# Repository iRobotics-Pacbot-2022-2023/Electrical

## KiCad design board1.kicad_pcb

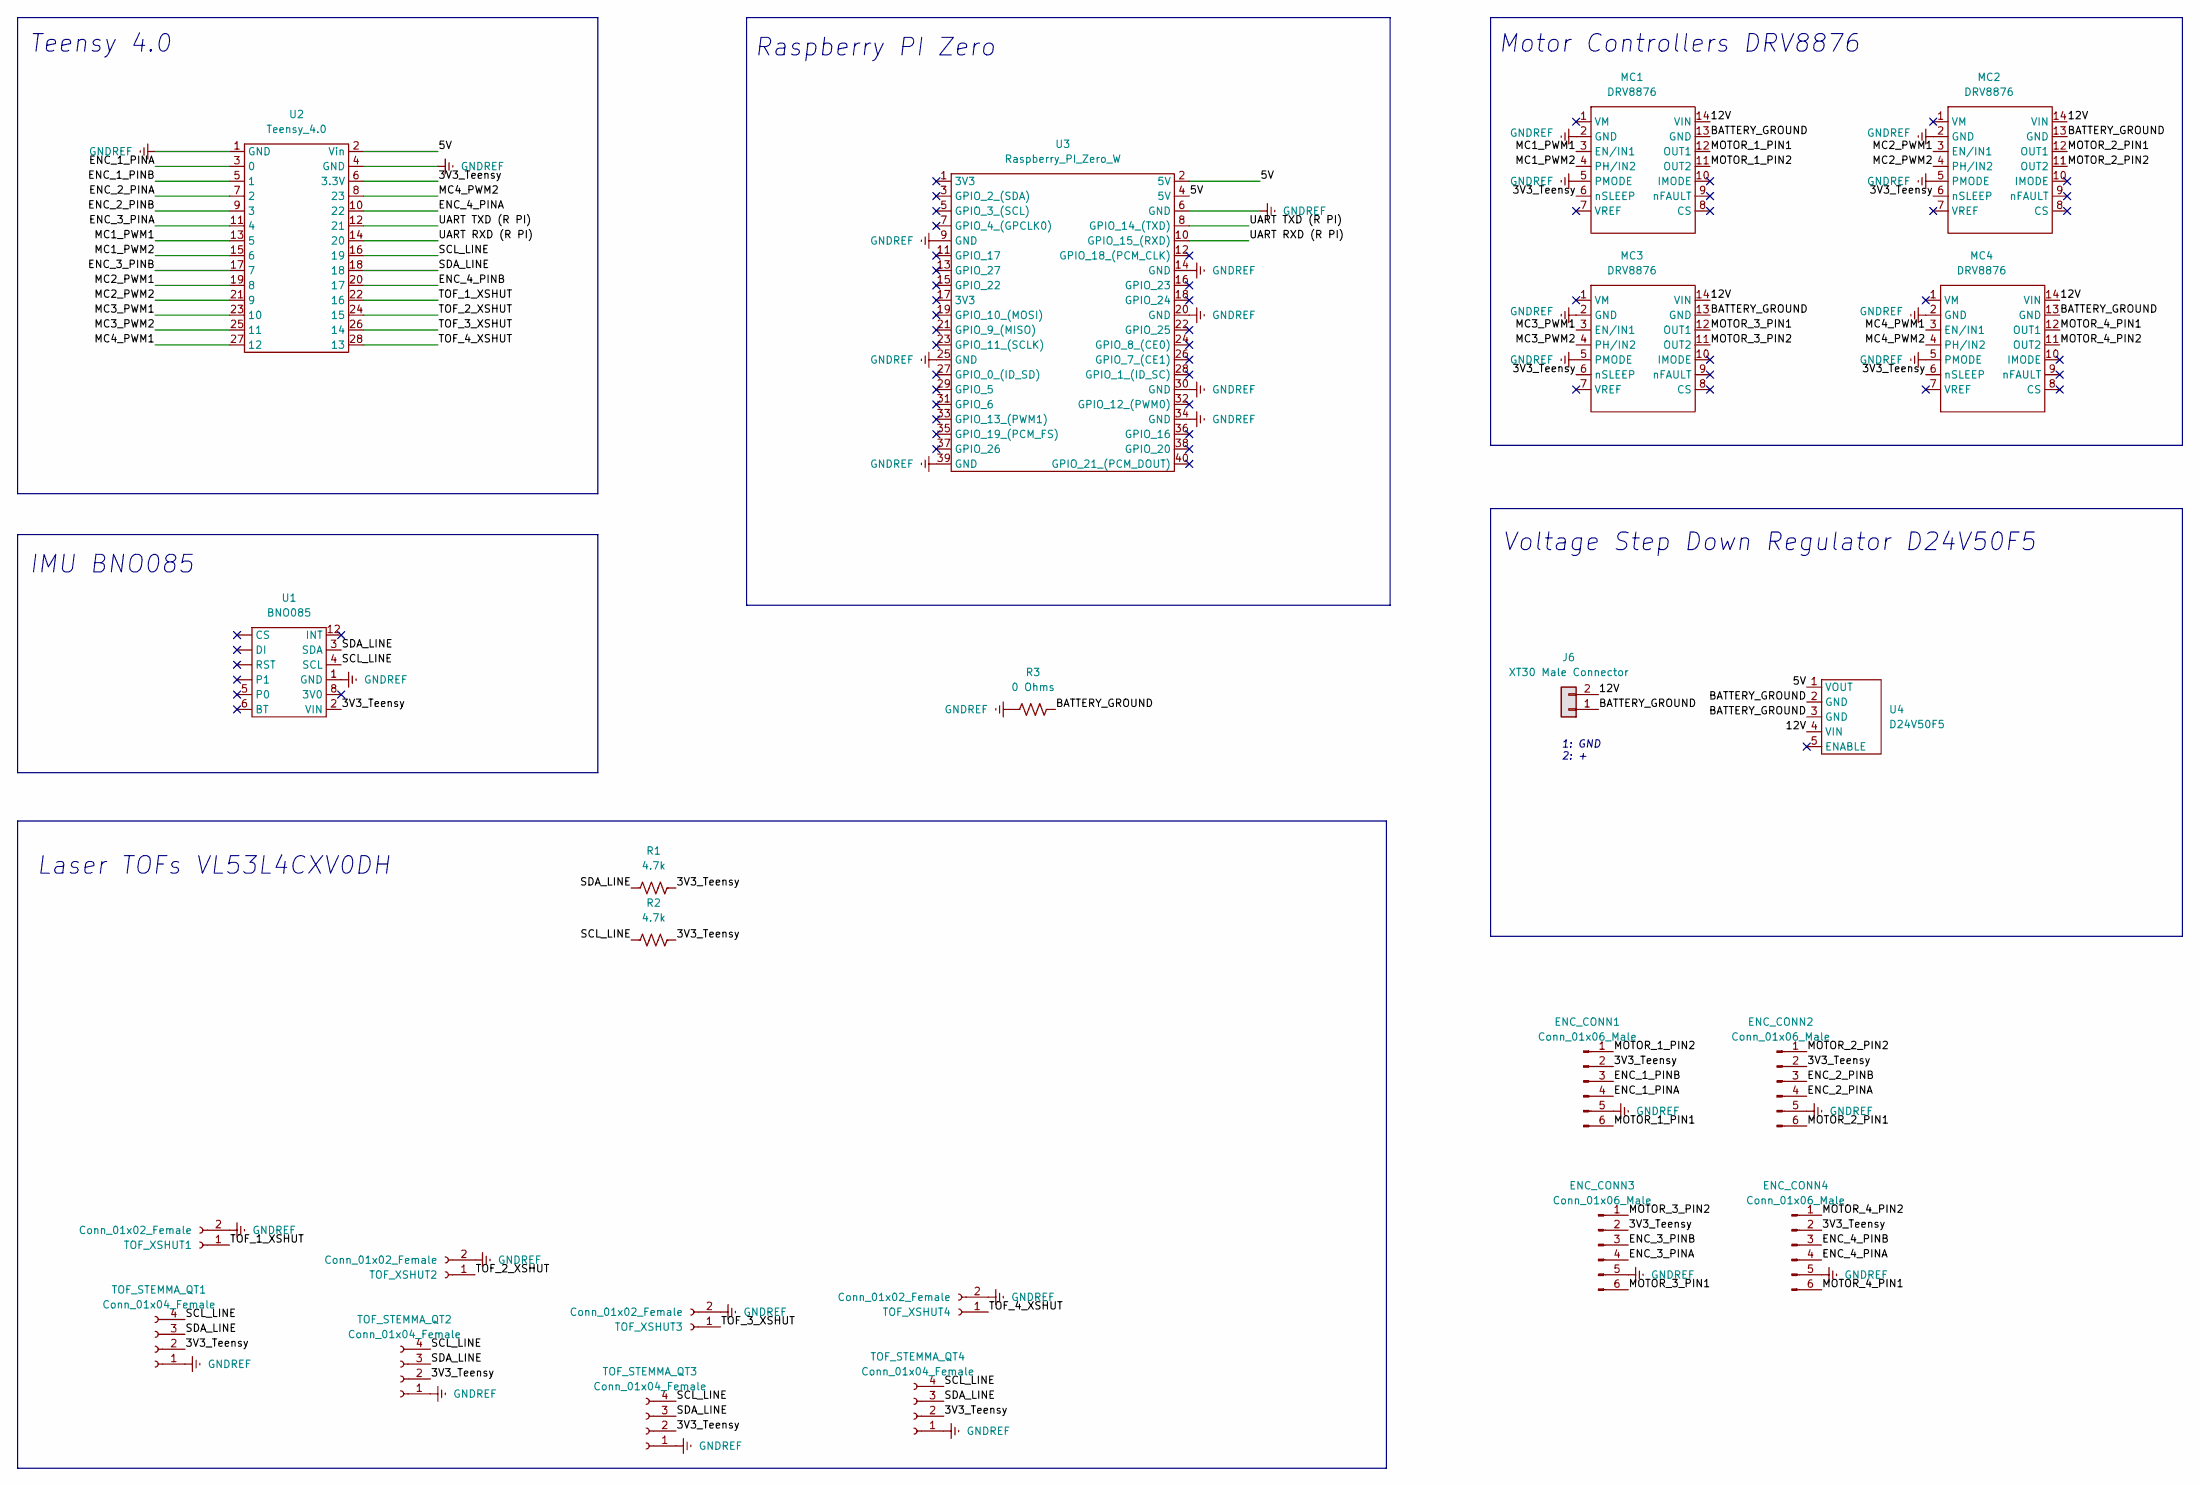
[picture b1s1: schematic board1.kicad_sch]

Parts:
ENC_CONN1: Conn_01x06_Male; PinHeader_1x06_P2.54mm_Vertical
ENC_CONN2, ENC_CONN3, ENC_CONN4: Conn_01x06_Male; PinSocket_1x06_P2.54mm_Vertical
J6: XT30 Male Connector; AMASS_XT30U-M_1x02_P5.0mm_Vertical
MC1, MC2, MC3, MC4: DRV8876
R1, R2: 4.7k; R_0805_2012Metric
R3: 0 Ohms; R_0805_2012Metric
TOF_STEMMA_QT1, TOF_STEMMA_QT2, TOF_STEMMA_QT3, TOF_STEMMA_QT4: Conn_01x04_Female; JST_SH_BM04B-SRSS-TB_1x04-1MP_P1.00mm_Vertical
TOF_XSHUT1, TOF_XSHUT2, TOF_XSHUT3, TOF_XSHUT4: Conn_01x02_Female; PinSocket_1x02_P2.54mm_Vertical
U1: BNO085; JST_SH_BM04B-SRSS-TB_1x04-1MP_P1.00mm_Vertical
U2: Teensy_4.0; Teensy 4.0
U3: Raspberry_PI_Zero_W; Raspberry Pi Zero W
U4: D24V50F5; Voltage Regulator D24V50F5

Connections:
/3V3_Teensy: ENC_CONN1.2, ENC_CONN2.2, ENC_CONN3.2, ENC_CONN4.2, MC1.6 (nSLEEP), MC2.6 (nSLEEP), MC3.6 (nSLEEP), MC4.6 (nSLEEP), R1.2, R2.2, TOF_STEMMA_QT1.2, TOF_STEMMA_QT2.2, TOF_STEMMA_QT3.2, TOF_STEMMA_QT4.2, U1.2 (VIN), U2.6 (3.3V)
/5V: U2.2 (Vin), U3.2 (5V), U3.4 (5V), U4.1 (VOUT)
/12V: J6.2, MC1.14 (VIN), MC2.14 (VIN), MC3.14 (VIN), MC4.14 (VIN), U4.4 (VIN)
/BATTERY_GROUND: J6.1, MC1.13 (GND), MC2.13 (GND), MC3.13 (GND), MC4.13 (GND), R3.2, U4.2 (GND), U4.3 (GND)
/ENC_1_PINA: ENC_CONN1.4, U2.3 (0)
/ENC_1_PINB: ENC_CONN1.3, U2.5 (1)
/ENC_2_PINA: ENC_CONN2.4, U2.7 (2)
/ENC_2_PINB: ENC_CONN2.3, U2.9 (3)
/ENC_3_PINA: ENC_CONN3.4, U2.11 (4)
/ENC_3_PINB: ENC_CONN3.3, U2.17 (7)
/ENC_4_PINA: ENC_CONN4.4, U2.10 (22)
/ENC_4_PINB: ENC_CONN4.3, U2.20 (17)
/MC1_PWM1: MC1.3 (EN/IN1), U2.13 (5)
/MC1_PWM2: MC1.4 (PH/IN2), U2.15 (6)
/MC2_PWM1: MC2.3 (EN/IN1), U2.19 (8)
/MC2_PWM2: MC2.4 (PH/IN2), U2.21 (9)
/MC3_PWM1: MC3.3 (EN/IN1), U2.23 (10)
/MC3_PWM2: MC3.4 (PH/IN2), U2.25 (11)
/MC4_PWM1: MC4.3 (EN/IN1), U2.27 (12)
/MC4_PWM2: MC4.4 (PH/IN2), U2.8 (23)
/MOTOR_1_PIN1: ENC_CONN1.6, MC1.12 (OUT1)
/MOTOR_1_PIN2: ENC_CONN1.1, MC1.11 (OUT2)
/MOTOR_2_PIN1: ENC_CONN2.6, MC2.12 (OUT1)
/MOTOR_2_PIN2: ENC_CONN2.1, MC2.11 (OUT2)
/MOTOR_3_PIN1: ENC_CONN3.6, MC3.12 (OUT1)
/MOTOR_3_PIN2: ENC_CONN3.1, MC3.11 (OUT2)
/MOTOR_4_PIN1: ENC_CONN4.6, MC4.12 (OUT1)
/MOTOR_4_PIN2: ENC_CONN4.1, MC4.11 (OUT2)
/SCL_LINE: R2.1, TOF_STEMMA_QT1.4, TOF_STEMMA_QT2.4, TOF_STEMMA_QT3.4, TOF_STEMMA_QT4.4, U1.4 (SCL), U2.16 (19)
/SDA_LINE: R1.1, TOF_STEMMA_QT1.3, TOF_STEMMA_QT2.3, TOF_STEMMA_QT3.3, TOF_STEMMA_QT4.3, U1.3 (SDA), U2.18
/TOF_1_XSHUT: TOF_XSHUT1.1, U2.22 (16)
/TOF_2_XSHUT: TOF_XSHUT2.1, U2.24 (15)
/TOF_3_XSHUT: TOF_XSHUT3.1, U2.26 (14)
/TOF_4_XSHUT: TOF_XSHUT4.1, U2.28 (13)
/UART RXD (R PI): U2.14 (20), U3.10 (GPIO_15_(RXD))
/UART TXD (R PI): U2.12 (21), U3.8 (GPIO_14_(TXD))
GNDREF: ENC_CONN1.5, ENC_CONN2.5, ENC_CONN3.5, ENC_CONN4.5, MC1.2 (GND), MC1.5 (PMODE), MC2.2 (GND), MC2.5 (PMODE), MC3.2 (GND), MC3.5 (PMODE), MC4.2 (GND), MC4.5 (PMODE), R3.1, TOF_STEMMA_QT1.1, TOF_STEMMA_QT2.1, TOF_STEMMA_QT3.1, TOF_STEMMA_QT4.1, TOF_XSHUT1.2, TOF_XSHUT2.2, TOF_XSHUT3.2, TOF_XSHUT4.2, U1.1 (GND), U2.1 (GND), U2.4 (GND), U3.6 (GND), U3.9 (GND), U3.14 (GND), U3.20 (GND), U3.25 (GND), U3.30 (GND), U3.34 (GND), U3.39 (GND)

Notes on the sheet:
Laser TOFs VL53L4CXV0DH
Teensy 4.0
1: GND 2: +
Motor Controllers DRV8876
Raspberry PI Zero
IMU BNO085
Voltage Step Down Regulator D24V50F5

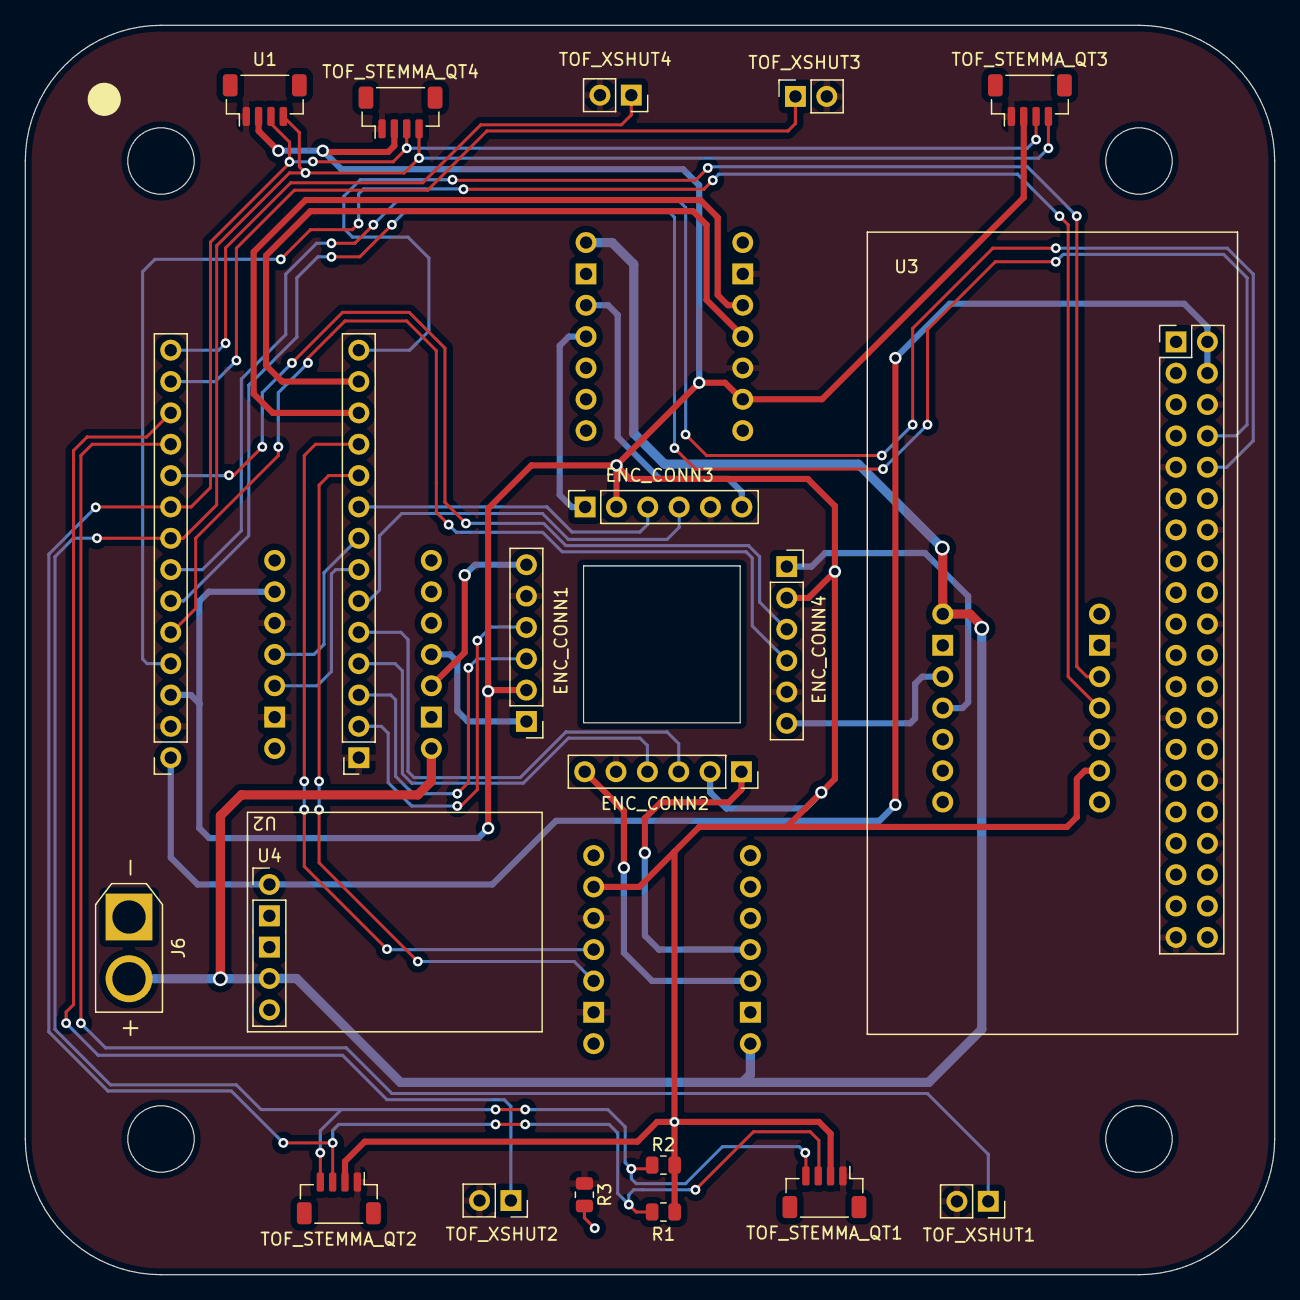
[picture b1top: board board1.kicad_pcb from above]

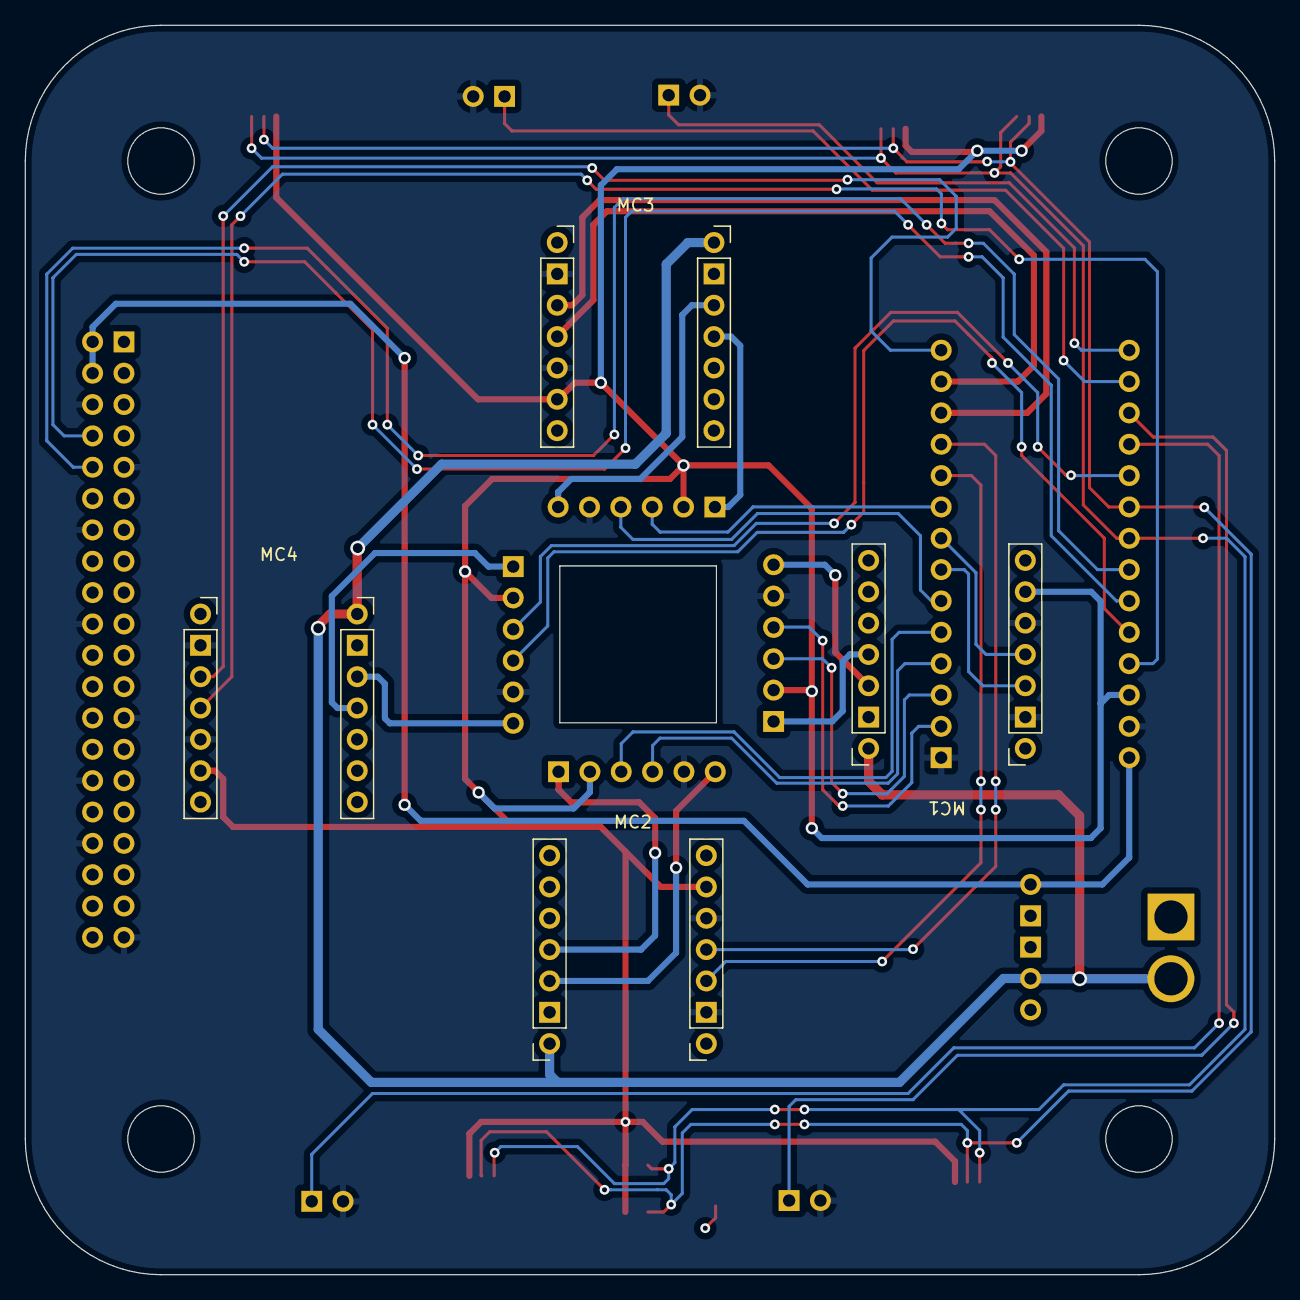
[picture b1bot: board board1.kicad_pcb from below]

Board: 4 copper layers, 101.2 x 101.2 mm, 24 parts (4 on the bottom side), 37 nets.

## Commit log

2022-12-03 Create test
2022-12-03 test commit and push
2022-12-03 Top Board
    Created Top Board KiCad project. Subject to renaming when boards are better understood.
2022-12-03 test push
2022-12-03 another test push
2022-12-03 test push on testbranch
2022-12-10 Top Board Management
    Leftover changes from creating top board? Pushing for now but will look into them
2022-12-10 Testing Symbol Library Creation
    Pushing a test symbol in order to test how symbol libraries work between kicad and github
2022-12-10 add new test symbol in symbol folders
2023-01-21 Created D24V50F5 Symbol
2023-01-21 DRV8876 KiCad Schematic Complete
2023-01-21 VL53L4CX TOF added
    Adafruit VL53L4CX TOF sensor added to symbol library
2023-01-21 Revert "Merge remote-tracking branch 'origin/tofsensor'"
    This reverts commit ec94c9f7a41ed07ffb1debeab3374b408ed38c8a, reversing
    changes made to 0f5a80eb67d65929ca78b85239dc9413235aba2e.
2023-01-21 Revert "Revert "Merge remote-tracking branch 'origin/tofsensor'""
    This reverts commit b3286974a6e237f4240251087869cf60ae62457c.
2023-01-21 Revert "Merge branch 'motor_controller_branch'"
    This reverts commit 0f5a80eb67d65929ca78b85239dc9413235aba2e, reversing
    changes made to cc46030deb95eece420e09bd20f8e198b64c1a43.
2023-01-21 added imu symbol
2023-01-28 test
2023-01-28 created C test
2023-01-28 created D test
2023-01-28 Removed Test Symbols
2023-01-28 adding imu symbol
2023-01-28 Create text
2023-01-28 Created Board1
2023-01-28 Created Board1 Libs
2023-01-28 Added tofsensor symbol
2023-01-28 modified imu symbol
2023-01-28 Created D24V50F5(5V regulator)
2023-02-04 added raspberry pi zero W symbol
2023-02-04 added raspberry pi and teensy symbols
2023-02-11 Motor driver symbol done
    DRV8876 Single Brushed DC Motor Driver Carrier
2023-02-11 Updated TOF sensor
2023-02-25 Updated Schematic
    Created zones for each individual part in the schematic and we decided on using hierarchal labels
2023-03-03 Created Physical Board Layout
    Created Edge Cuts for Physical Board
    Layout based off of Rushil's drawing
2023-03-03 Updated Edge Cuts
    Updated edge cuts with updated dimensions
2023-03-04 Connected RPI to Teensy SPI
2023-03-04 created footprint library and motor controller pinheader
2023-03-04 Added library
2023-03-04 Added SDA and SCL to IMU
2023-03-04 modified motor controller footprint and created IMU footprint
2023-03-04 created teensy footprint
2023-03-04 created rasp pi footprint
2023-03-07 stuff
2023-03-07 pcb layed out, need help with ratsnest
2023-03-09 Updated Footprints
    Updated Footprints to indicate physical limitations of components
2023-03-09 updated board pcb to better match physical constraints
2023-03-09 slight edits
2023-03-10 made changes
2023-03-14 preliminary routing of traces
2023-03-15 Routed PCB
    routed pcb
2023-03-16 Updated PCB
    Flipped Encoder, Increased Trace Size, and Changed Resistors to be 0805
2023-03-17 added ground layer and is now 4 layer pcb
2023-03-17 Added suggestion for 4 layer board
2023-03-17 additional changes
2023-03-19 updated board to be 90x90, new board can be found in the folder "90x90"
